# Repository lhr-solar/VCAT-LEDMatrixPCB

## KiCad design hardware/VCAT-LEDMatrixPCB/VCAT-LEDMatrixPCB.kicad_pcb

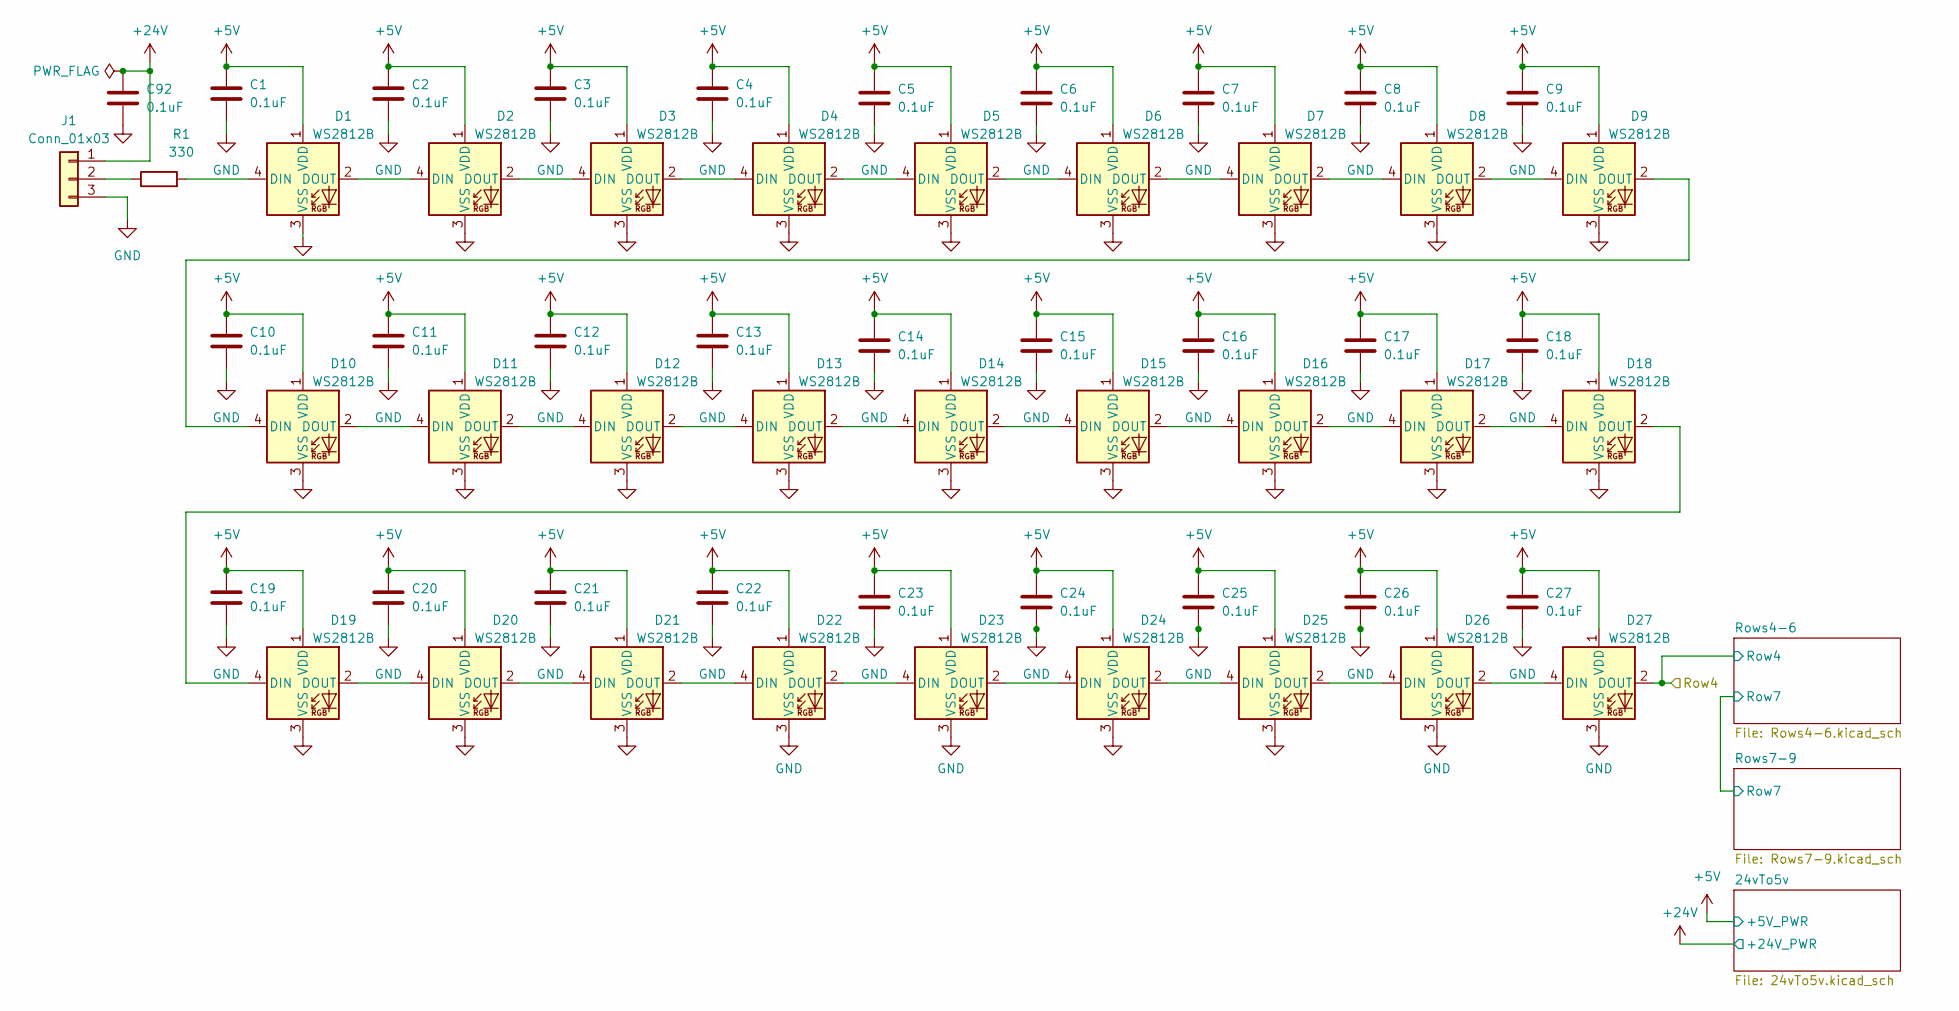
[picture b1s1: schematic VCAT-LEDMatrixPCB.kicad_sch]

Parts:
C1, C2, C3, C4, C5, C6, C7, C8, C9, C10, C11, C12, C13, C14, C15, C16, C17, C18, C19, C20, C21, C22, C23, C24, C25, C26, C27, C92: 0.1uF; C_0603_1608Metric
D1, D2, D3, D4, D5, D6, D7, D8, D9, D10, D11, D12, D13, D14, D15, D16, D17, D18, D19, D20, D21, D22, D23, D24, D25, D26, D27: WS2812B; LED_WS2812B_PLCC4_5.0x5.0mm_P3.2mm
J1: Conn_01x03; 105313-1103
R1: 330; R_0603_1608Metric

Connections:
+5V: C1.1, C2.1, C3.1, C4.1, C5.1, C6.1, C7.1, C8.1, C9.1, C10.1, C11.1, C12.1, C13.1, C14.1, C15.1, C16.1, C17.1, C18.1, C19.1, C20.1, C21.1, C22.1, C23.1, C24.1, C25.1, C26.1, C27.1, D1.1 (VDD), D2.1 (VDD), D3.1 (VDD), D4.1 (VDD), D5.1 (VDD), D6.1 (VDD), D7.1 (VDD), D8.1 (VDD), D9.1 (VDD), D10.1 (VDD), D11.1 (VDD), D12.1 (VDD), D13.1 (VDD), D14.1 (VDD), D15.1 (VDD), D16.1 (VDD), D17.1 (VDD), D18.1 (VDD), D19.1 (VDD), D20.1 (VDD), D21.1 (VDD), D22.1 (VDD), D23.1 (VDD), D24.1 (VDD), D25.1 (VDD), D26.1 (VDD), D27.1 (VDD); also elsewhere on the board
+24V: C92.1, J1.1; also elsewhere on the board
/Row4: D27.2 (DOUT); also elsewhere on the board
GND: C1.2, C2.2, C3.2, C4.2, C5.2, C6.2, C7.2, C8.2, C9.2, C10.2, C11.2, C12.2, C13.2, C14.2, C15.2, C16.2, C17.2, C18.2, C19.2, C20.2, C21.2, C22.2, C23.2, C24.2, C25.2, C26.2, C27.2, C92.2, D1.3 (VSS), D2.3 (VSS), D3.3 (VSS), D4.3 (VSS), D5.3 (VSS), D6.3 (VSS), D7.3 (VSS), D8.3 (VSS), D9.3 (VSS), D10.3 (VSS), D11.3 (VSS), D12.3 (VSS), D13.3 (VSS), D14.3 (VSS), D15.3 (VSS), D16.3 (VSS), D17.3 (VSS), D18.3 (VSS), D19.3 (VSS), D20.3 (VSS), D21.3 (VSS), D22.3 (VSS), D23.3 (VSS), D24.3 (VSS), D25.3 (VSS), D26.3 (VSS), D27.3 (VSS), J1.3; also elsewhere on the board
unnamed: D1.4 (DIN), R1.2
unnamed: D1.2 (DOUT), D2.4 (DIN)
unnamed: D2.2 (DOUT), D3.4 (DIN)
unnamed: D3.2 (DOUT), D4.4 (DIN)
unnamed: D4.2 (DOUT), D5.4 (DIN)
unnamed: D5.2 (DOUT), D6.4 (DIN)
unnamed: D6.2 (DOUT), D7.4 (DIN)
unnamed: D7.2 (DOUT), D8.4 (DIN)
unnamed: D8.2 (DOUT), D9.4 (DIN)
unnamed: D9.2 (DOUT), D10.4 (DIN)
unnamed: D10.2 (DOUT), D11.4 (DIN)
unnamed: D11.2 (DOUT), D12.4 (DIN)
unnamed: D12.2 (DOUT), D13.4 (DIN)
unnamed: D13.2 (DOUT), D14.4 (DIN)
unnamed: D14.2 (DOUT), D15.4 (DIN)
unnamed: D15.2 (DOUT), D16.4 (DIN)
unnamed: D16.2 (DOUT), D17.4 (DIN)
unnamed: D17.2 (DOUT), D18.4 (DIN)
unnamed: D18.2 (DOUT), D19.4 (DIN)
unnamed: D19.2 (DOUT), D20.4 (DIN)
unnamed: D20.2 (DOUT), D21.4 (DIN)
unnamed: D21.2 (DOUT), D22.4 (DIN)
unnamed: D22.2 (DOUT), D23.4 (DIN)
unnamed: D23.2 (DOUT), D24.4 (DIN)
unnamed: D24.2 (DOUT), D25.4 (DIN)
unnamed: D25.2 (DOUT), D26.4 (DIN)
unnamed: D26.2 (DOUT), D27.4 (DIN)
unnamed: J1.2, R1.1

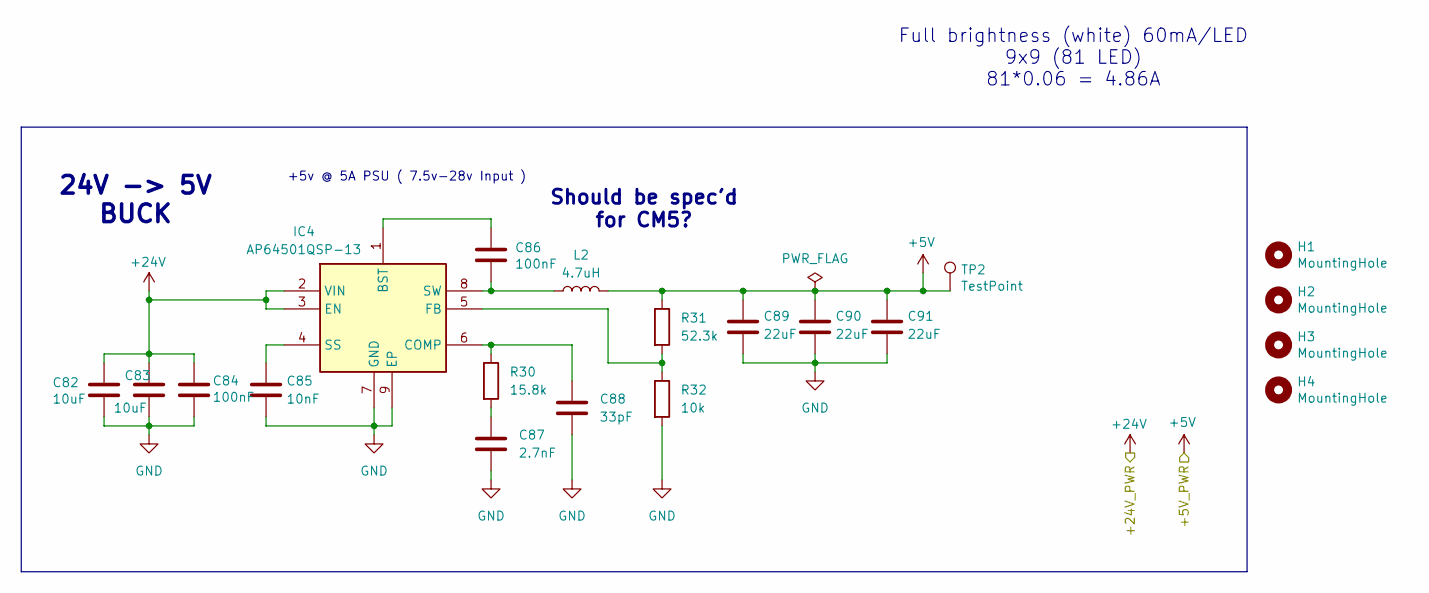
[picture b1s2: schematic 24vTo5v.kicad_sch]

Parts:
C82, C83: 10uF; C_0603_1608Metric; JLC C440198
C84, C86: 100nF; C_0603_1608Metric; JLC C14663
C85: 10nF; C_0603_1608Metric; JLC C1589
C87: 2.7nF; C_0603_1608Metric; JLC C107085
C88: 33pF; C_0603_1608Metric; JLC C1663
C89, C90, C91: 22uF; C_0603_1608Metric; JLC C338078
H1, H2, H3, H4: MountingHole; MountingHole_3.2mm_M3; JLC N/A
IC4: AP64501QSP-13; SOIC127P600X163-9N; JLC C2071517
L2: 4.7uH; INDPM110100X540N; JLC C19947673
R30: 15.8k; R_0603_1608Metric; JLC C17468
R31: 52.3k; R_0603_1608Metric; JLC C22369875
R32: 10k; R_0603_1608Metric; JLC C17414
TP2: TestPoint; TestPoint_Keystone_5005-5009_Compact; JLC N/A

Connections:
+5V: C89.1, C90.1, C91.1, L2.2, R31.1, TP2.1; also elsewhere on the board
+24V: C82.1, C83.1, C84.1, IC4.2 (VIN), IC4.3 (EN); also elsewhere on the board
GND: C82.2, C83.2, C84.2, C85.2, C87.2, C88.2, C89.2, C90.2, C91.2, IC4.7 (GND), IC4.9 (EP), R32.2; also elsewhere on the board
unnamed: C87.1, R30.2
unnamed: C86.1, IC4.1 (BST)
unnamed: C88.1, IC4.6 (COMP), R30.1
unnamed: IC4.5 (FB), R31.2, R32.1
unnamed: C85.1, IC4.4 (SS)
unnamed: C86.2, IC4.8 (SW), L2.1

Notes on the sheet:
24V -> 5V BUCK
+5v @ 5A PSU ( 7.5v-28v Input )
Should be spec'd for CM5?
Full brightness (white) 60mA/LED 9x9 (81 LED) 81*0.06 = 4.86A

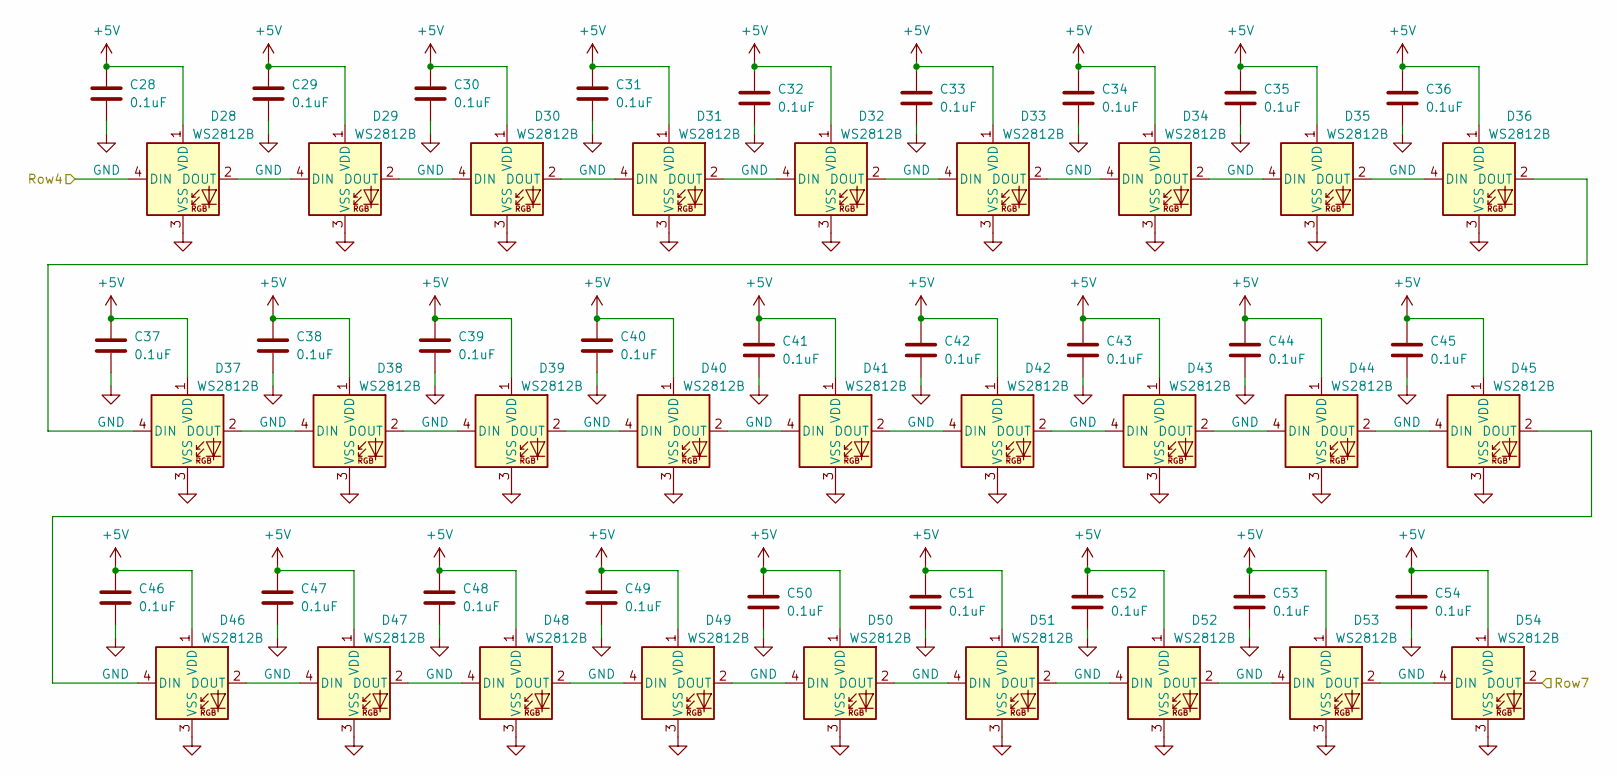
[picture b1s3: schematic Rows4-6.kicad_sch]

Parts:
C28, C29, C30, C31, C32, C33, C34, C35, C36, C37, C38, C39, C40, C41, C42, C43, C44, C45, C46, C47, C48, C49, C50, C51, C52, C53, C54: 0.1uF; C_0603_1608Metric
D28, D29, D30, D31, D32, D33, D34, D35, D36, D37, D38, D39, D40, D41, D42, D43, D44, D45, D46, D47, D48, D49, D50, D51, D52, D53, D54: WS2812B; LED_WS2812B_PLCC4_5.0x5.0mm_P3.2mm

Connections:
+5V: C28.1, C29.1, C30.1, C31.1, C32.1, C33.1, C34.1, C35.1, C36.1, C37.1, C38.1, C39.1, C40.1, C41.1, C42.1, C43.1, C44.1, C45.1, C46.1, C47.1, C48.1, C49.1, C50.1, C51.1, C52.1, C53.1, C54.1, D28.1 (VDD), D29.1 (VDD), D30.1 (VDD), D31.1 (VDD), D32.1 (VDD), D33.1 (VDD), D34.1 (VDD), D35.1 (VDD), D36.1 (VDD), D37.1 (VDD), D38.1 (VDD), D39.1 (VDD), D40.1 (VDD), D41.1 (VDD), D42.1 (VDD), D43.1 (VDD), D44.1 (VDD), D45.1 (VDD), D46.1 (VDD), D47.1 (VDD), D48.1 (VDD), D49.1 (VDD), D50.1 (VDD), D51.1 (VDD), D52.1 (VDD), D53.1 (VDD), D54.1 (VDD); also elsewhere on the board
/Row4: D28.4 (DIN); also elsewhere on the board
/Rows4-6/Row7: D54.2 (DOUT); also elsewhere on the board
GND: C28.2, C29.2, C30.2, C31.2, C32.2, C33.2, C34.2, C35.2, C36.2, C37.2, C38.2, C39.2, C40.2, C41.2, C42.2, C43.2, C44.2, C45.2, C46.2, C47.2, C48.2, C49.2, C50.2, C51.2, C52.2, C53.2, C54.2, D28.3 (VSS), D29.3 (VSS), D30.3 (VSS), D31.3 (VSS), D32.3 (VSS), D33.3 (VSS), D34.3 (VSS), D35.3 (VSS), D36.3 (VSS), D37.3 (VSS), D38.3 (VSS), D39.3 (VSS), D40.3 (VSS), D41.3 (VSS), D42.3 (VSS), D43.3 (VSS), D44.3 (VSS), D45.3 (VSS), D46.3 (VSS), D47.3 (VSS), D48.3 (VSS), D49.3 (VSS), D50.3 (VSS), D51.3 (VSS), D52.3 (VSS), D53.3 (VSS), D54.3 (VSS); also elsewhere on the board
unnamed: D28.2 (DOUT), D29.4 (DIN)
unnamed: D29.2 (DOUT), D30.4 (DIN)
unnamed: D30.2 (DOUT), D31.4 (DIN)
unnamed: D31.2 (DOUT), D32.4 (DIN)
unnamed: D32.2 (DOUT), D33.4 (DIN)
unnamed: D33.2 (DOUT), D34.4 (DIN)
unnamed: D34.2 (DOUT), D35.4 (DIN)
unnamed: D35.2 (DOUT), D36.4 (DIN)
unnamed: D36.2 (DOUT), D37.4 (DIN)
unnamed: D37.2 (DOUT), D38.4 (DIN)
unnamed: D38.2 (DOUT), D39.4 (DIN)
unnamed: D39.2 (DOUT), D40.4 (DIN)
unnamed: D40.2 (DOUT), D41.4 (DIN)
unnamed: D41.2 (DOUT), D42.4 (DIN)
unnamed: D42.2 (DOUT), D43.4 (DIN)
unnamed: D43.2 (DOUT), D44.4 (DIN)
unnamed: D44.2 (DOUT), D45.4 (DIN)
unnamed: D45.2 (DOUT), D46.4 (DIN)
unnamed: D46.2 (DOUT), D47.4 (DIN)
unnamed: D47.2 (DOUT), D48.4 (DIN)
unnamed: D48.2 (DOUT), D49.4 (DIN)
unnamed: D49.2 (DOUT), D50.4 (DIN)
unnamed: D50.2 (DOUT), D51.4 (DIN)
unnamed: D51.2 (DOUT), D52.4 (DIN)
unnamed: D52.2 (DOUT), D53.4 (DIN)
unnamed: D53.2 (DOUT), D54.4 (DIN)

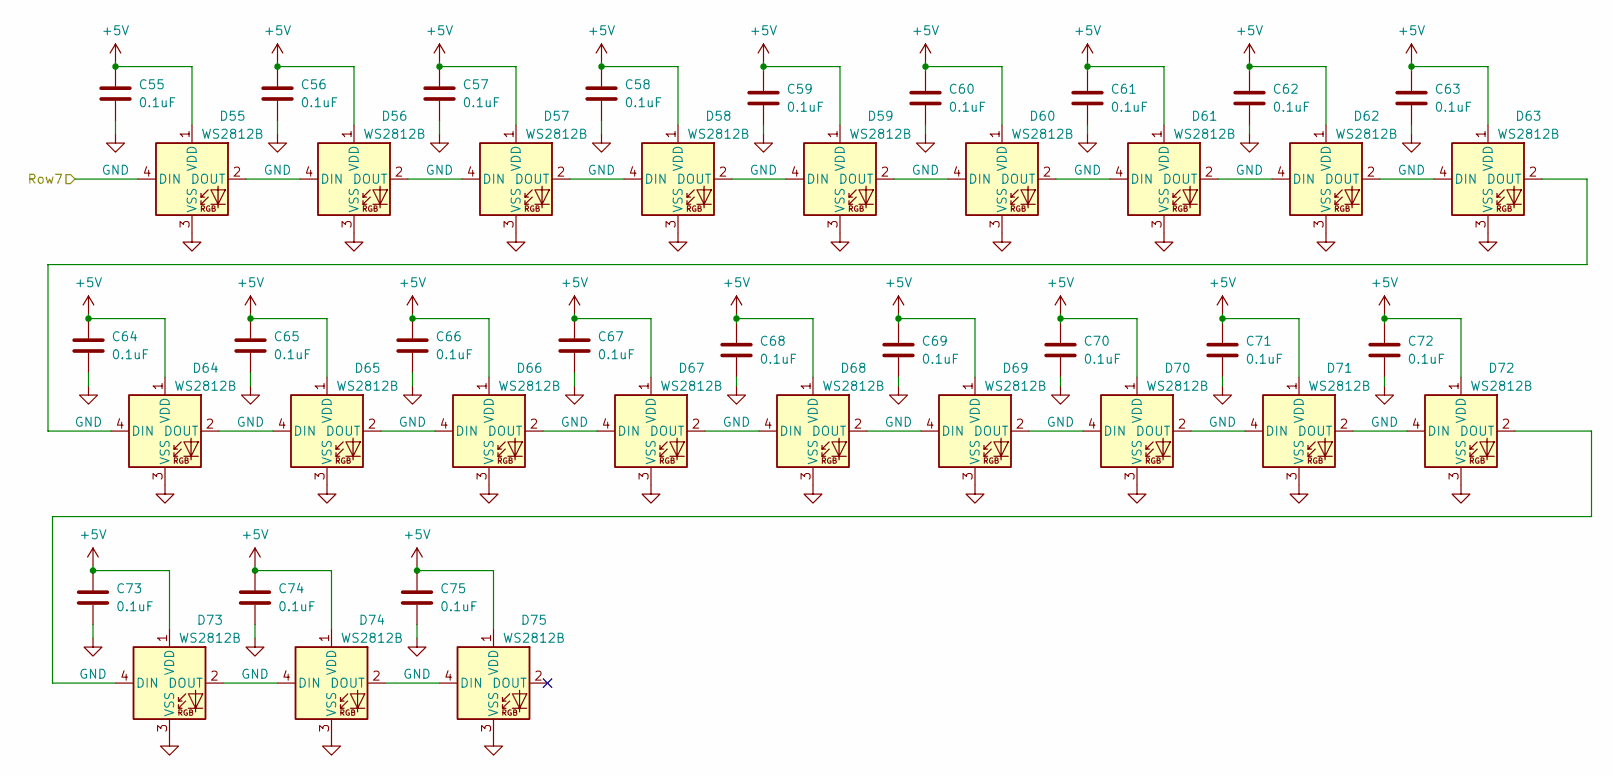
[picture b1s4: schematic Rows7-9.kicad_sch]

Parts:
C55, C56, C57, C58, C59, C60, C61, C62, C63, C64, C65, C66, C67, C68, C69, C70, C71, C72, C73, C74, C75: 0.1uF; C_0603_1608Metric
D55, D56, D57, D58, D59, D60, D61, D62, D63, D64, D65, D66, D67, D68, D69, D70, D71, D72, D73, D74, D75: WS2812B; LED_WS2812B_PLCC4_5.0x5.0mm_P3.2mm

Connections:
+5V: C55.1, C56.1, C57.1, C58.1, C59.1, C60.1, C61.1, C62.1, C63.1, C64.1, C65.1, C66.1, C67.1, C68.1, C69.1, C70.1, C71.1, C72.1, C73.1, C74.1, C75.1, D55.1 (VDD), D56.1 (VDD), D57.1 (VDD), D58.1 (VDD), D59.1 (VDD), D60.1 (VDD), D61.1 (VDD), D62.1 (VDD), D63.1 (VDD), D64.1 (VDD), D65.1 (VDD), D66.1 (VDD), D67.1 (VDD), D68.1 (VDD), D69.1 (VDD), D70.1 (VDD), D71.1 (VDD), D72.1 (VDD), D73.1 (VDD), D74.1 (VDD), D75.1 (VDD); also elsewhere on the board
/Rows4-6/Row7: D55.4 (DIN); also elsewhere on the board
GND: C55.2, C56.2, C57.2, C58.2, C59.2, C60.2, C61.2, C62.2, C63.2, C64.2, C65.2, C66.2, C67.2, C68.2, C69.2, C70.2, C71.2, C72.2, C73.2, C74.2, C75.2, D55.3 (VSS), D56.3 (VSS), D57.3 (VSS), D58.3 (VSS), D59.3 (VSS), D60.3 (VSS), D61.3 (VSS), D62.3 (VSS), D63.3 (VSS), D64.3 (VSS), D65.3 (VSS), D66.3 (VSS), D67.3 (VSS), D68.3 (VSS), D69.3 (VSS), D70.3 (VSS), D71.3 (VSS), D72.3 (VSS), D73.3 (VSS), D74.3 (VSS), D75.3 (VSS); also elsewhere on the board
unnamed: D55.2 (DOUT), D56.4 (DIN)
unnamed: D56.2 (DOUT), D57.4 (DIN)
unnamed: D57.2 (DOUT), D58.4 (DIN)
unnamed: D58.2 (DOUT), D59.4 (DIN)
unnamed: D59.2 (DOUT), D60.4 (DIN)
unnamed: D60.2 (DOUT), D61.4 (DIN)
unnamed: D61.2 (DOUT), D62.4 (DIN)
unnamed: D62.2 (DOUT), D63.4 (DIN)
unnamed: D63.2 (DOUT), D64.4 (DIN)
unnamed: D64.2 (DOUT), D65.4 (DIN)
unnamed: D65.2 (DOUT), D66.4 (DIN)
unnamed: D66.2 (DOUT), D67.4 (DIN)
unnamed: D67.2 (DOUT), D68.4 (DIN)
unnamed: D68.2 (DOUT), D69.4 (DIN)
unnamed: D69.2 (DOUT), D70.4 (DIN)
unnamed: D70.2 (DOUT), D71.4 (DIN)
unnamed: D71.2 (DOUT), D72.4 (DIN)
unnamed: D72.2 (DOUT), D73.4 (DIN)
unnamed: D73.2 (DOUT), D74.4 (DIN)
unnamed: D74.2 (DOUT), D75.4 (DIN)

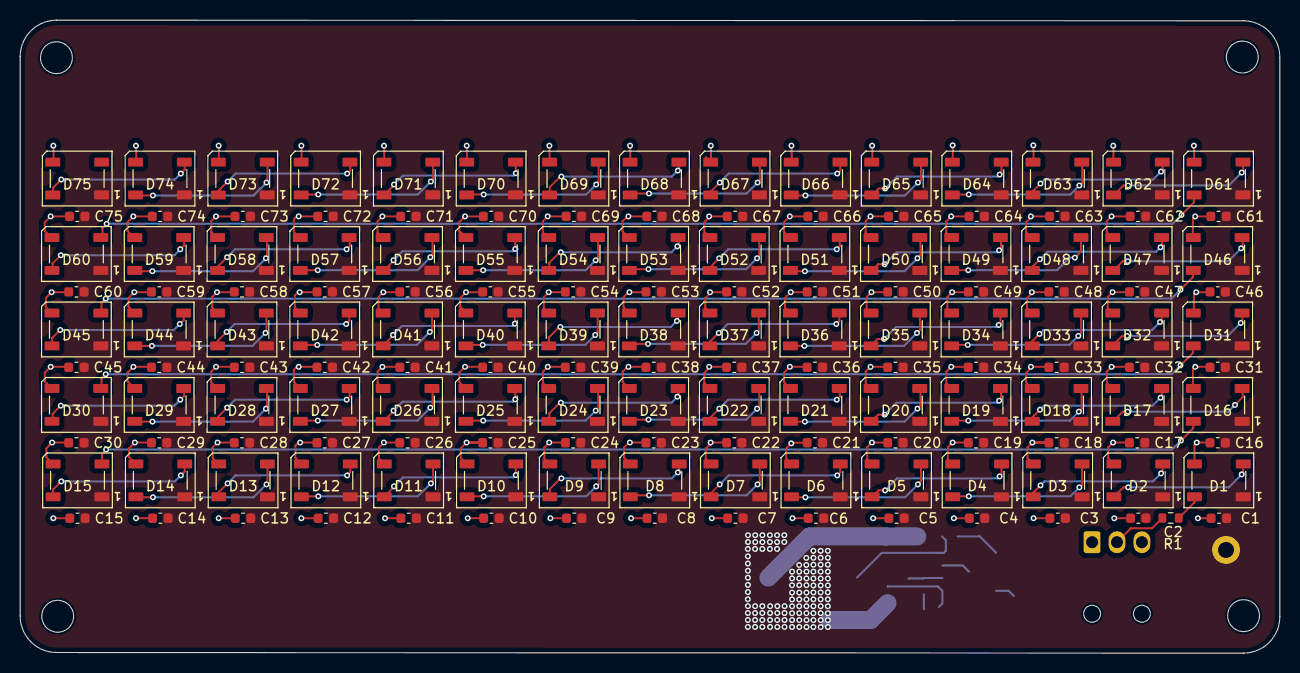
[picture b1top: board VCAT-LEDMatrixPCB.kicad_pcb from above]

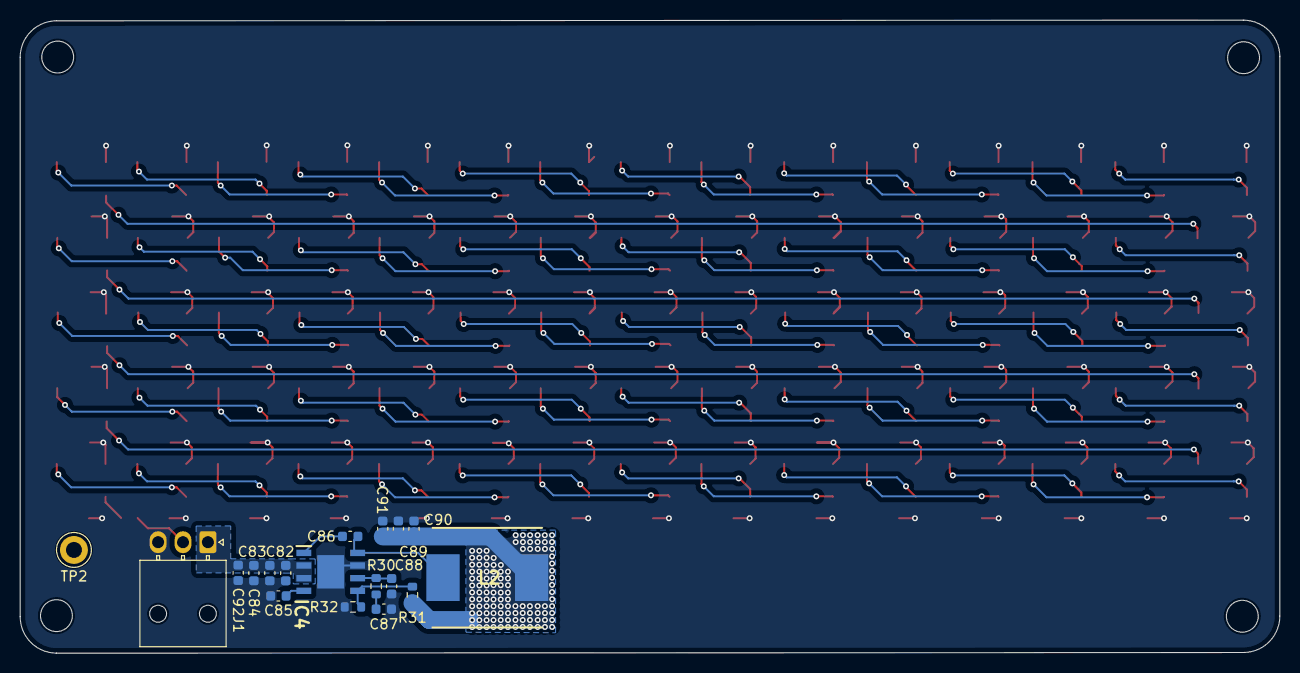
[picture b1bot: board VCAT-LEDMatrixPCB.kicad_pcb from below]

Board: 2 copper layers, 126.5 x 63.5 mm, 173 parts (18 on the bottom side), 85 nets.

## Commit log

2026-01-31 Schematic Review
2026-01-31 Removed KiCad sharepoint
2026-02-03 Layout 50% done
2026-02-03 Layout Review
2026-02-03 Layout Review without Bom
2026-02-04 Added Vias and made board symmetrical
2026-02-04 Review without Bom
2026-02-04 overall review
